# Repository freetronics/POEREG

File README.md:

Power-over-Ethernet 802.3af Regulator
=====================================

Module to regulate power supplied on Power-over-Ethernet connection
down to 10Vdc for supply to the on-board voltage regulator in an
Arduino Uno or other compatible board using the Freetronics Ethernet
Shield, or boards with onboard Ethernet such as the Freetronics
EtherTen, EtherMega, and EtherDue.

The output can optionally be switched to 12V which can be useful for
supplying power to external loads such as 12V relays.

Features:

 * Adds 802.3af-compliant Power-over-Ethernet "PD" (powered device)
   support to the Freetronics Ethernet shield and other Freetronics
   boards.
 * Input voltage range 36-57Vdc (nominal 48Vdc for 802.3af PoE)
 * Output voltage regulated to 10V and fed to Arduino on-board voltage
   regulator via Ethernet shield for further regulation down to 5V.
 * Plugs directly onto Freetronics Ethernet Shield and other
   Freetronics boards.
 * "Power on" LED.

More information at:

  http://www.freetronics.com.au/poereg

Hardware
--------
The "Hardware" directory contains the PCB design as an EAGLE project.
EAGLE PCB design software is available from Autodesk free for
non-commercial use.

Credits
-------
  * Jonathan Oxer <jon@oxer.com.au>

License
-------
Copyright 2010-2021 Freetronics Pty Ltd www.freetronics.com

The hardware portion of this project is licensed under the TAPR Open
Hardware License (www.tapr.org/OHL). The "license" folder within this
repository also contains a copy of this license in plain text format.

The software portion of this project is licensed under the Simplified
BSD License. The "licence" folder within this project contains a
copy of this license in plain text format.

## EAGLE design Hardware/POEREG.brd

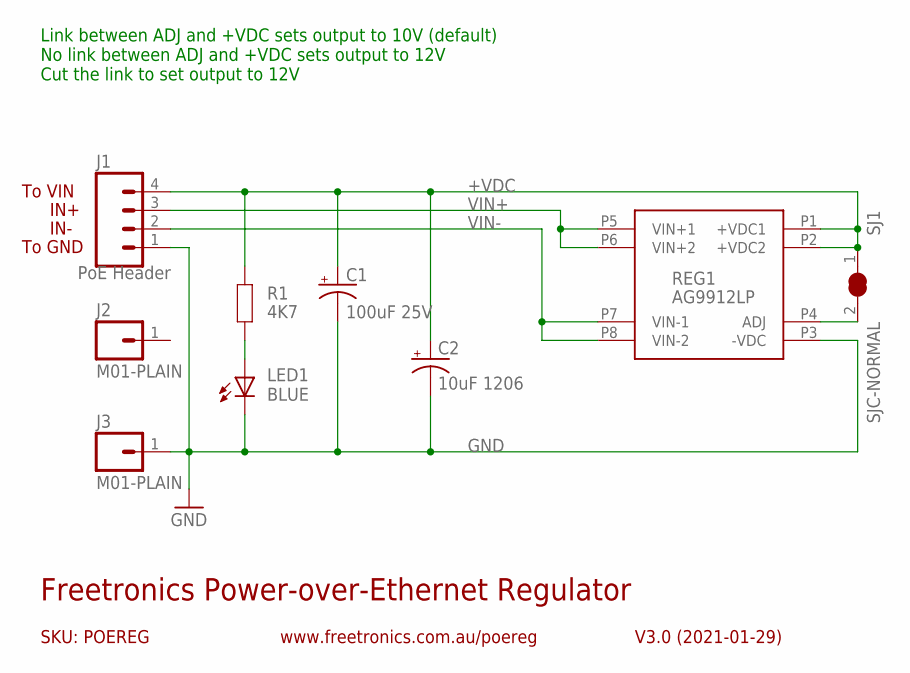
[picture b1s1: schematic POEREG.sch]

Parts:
C1: 100uF 25V; PANASONIC_D
C2: 10uF 1206; EIA3216
J1: PoE Header; 1X04
J2, J3: M01-PLAIN; 1X01
LED1: BLUE; LED-0603
R1: 4K7; R0603
REG1: AG9912LP; AG9900LP
SJ1: SJC-NORMAL; SJC

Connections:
+VDC: C1.+, C2.A (+), J1.4, R1.1, REG1.P1 (+VDC1), REG1.P2 (+VDC2), SJ1.1
GND: C1.-, C2.C (-), J1.1, J3.1, LED1.C, REG1.P3 (-VDC)
unnamed: REG1.P4 (ADJ), SJ1.2
unnamed: LED1.A, R1.2
VIN+: J1.3, REG1.P5 (VIN+1), REG1.P6 (VIN+2)
VIN-: J1.2, REG1.P7 (VIN-1), REG1.P8 (VIN-2)

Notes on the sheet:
Freetronics Power-over-Ethernet Regulator
V3.0 (2021-01-29)
www.freetronics.com.au/poereg
SKU: POEREG
To VIN
IN+
IN-
To GND
Link between ADJ and +VDC sets output to 10V (default) No link between ADJ and +VDC sets output to 12V Cut the link to set output to 12V

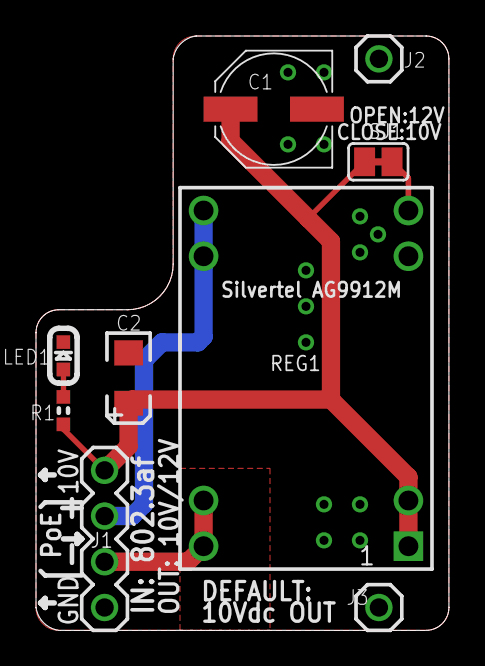
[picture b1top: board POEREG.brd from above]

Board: 2 copper layers, 22.9 x 33.0 mm, 9 parts (0 on the bottom side), 6 nets.

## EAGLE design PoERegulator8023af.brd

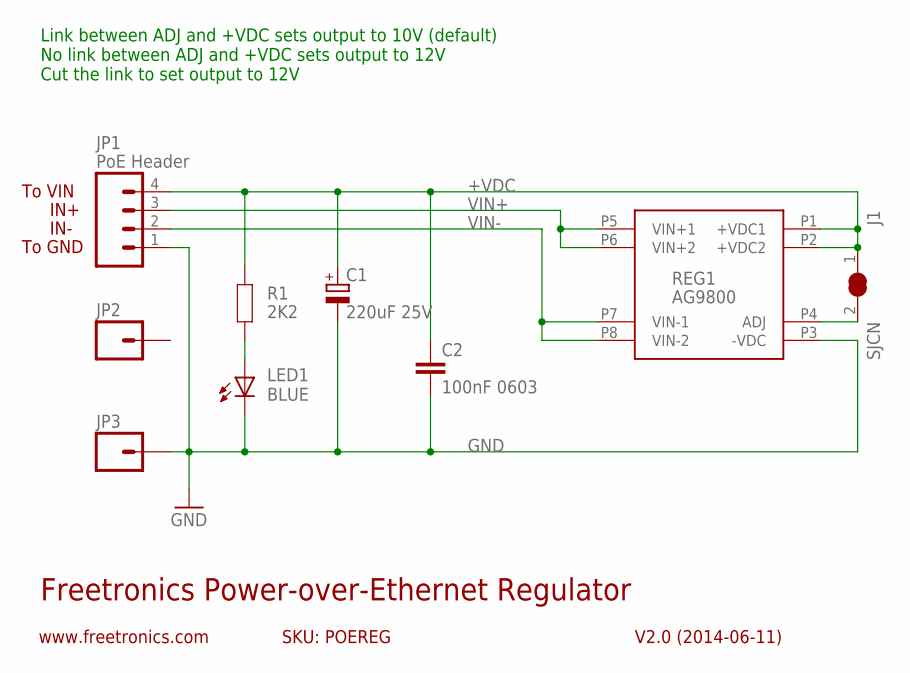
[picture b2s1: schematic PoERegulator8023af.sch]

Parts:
C1: 220uF 25V; PANASONIC_D
C2: 100nF 0603; 0603
J1: SJCN; SJC
JP1: PoE Header; 1X04
JP2, JP3: M01PTH; 1X01
LED1: BLUE; LED-0603
R1: 2K2; 0603
REG1: AG9800

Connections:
+VDC: C1.+, C2.1, J1.1, JP1.4, R1.1, REG1.P1 (+VDC1), REG1.P2 (+VDC2)
GND: C1.-, C2.2, JP1.1, JP3.1, LED1.C, REG1.P3 (-VDC)
unnamed: J1.2, REG1.P4 (ADJ)
unnamed: LED1.A, R1.2
VIN+: JP1.3, REG1.P5 (VIN+1), REG1.P6 (VIN+2)
VIN-: JP1.2, REG1.P7 (VIN-1), REG1.P8 (VIN-2)

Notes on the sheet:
Freetronics Power-over-Ethernet Regulator
V2.0 (2014-06-11)
www.freetronics.com
SKU: POEREG
To VIN
IN+
IN-
To GND
Link between ADJ and +VDC sets output to 10V (default) No link between ADJ and +VDC sets output to 12V Cut the link to set output to 12V

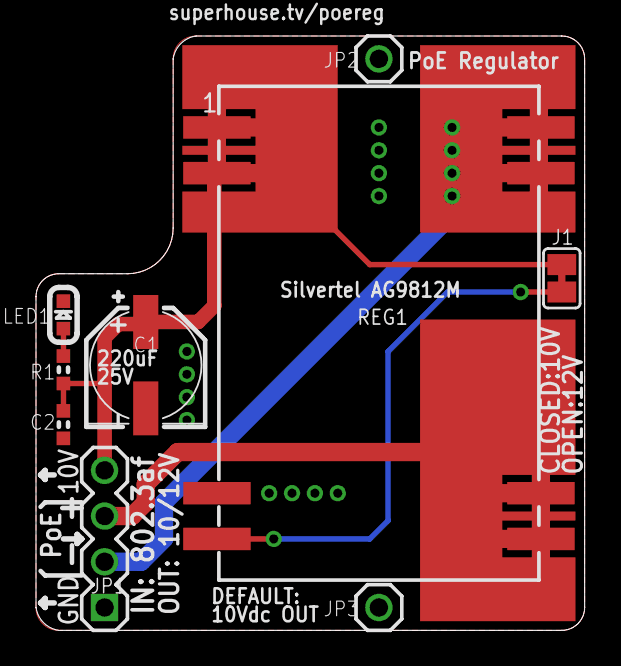
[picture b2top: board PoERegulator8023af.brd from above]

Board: 2 copper layers, 30.5 x 33.0 mm, 9 parts (0 on the bottom side), 6 nets.

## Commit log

2010-07-28 Initial import of project
2010-09-14 Updated reg part to have correct footprint
2010-09-14 Major board rearrangement, only partly done
2010-09-24 Changed output to 7.5V and finished routing
2010-09-26 Final positioning tweaks
2010-10-05 Fixed reference to output voltage
2014-06-10 Added option to change output to 12V
2014-06-10 Updated README for v2.0
2014-06-11 Replaced Silvertel AG8112M with AG9812M for v2.0 release
2016-05-26 Improved position of part value labels
2018-01-10 Updated docs for new branding
2019-04-24 Fixed fonts for silkscreen and schematic
2021-01-29 Renamed hardware files to match SKU.
2021-01-29 Replace Silvertel module with AG9912LP.
2021-01-29 Updated formatting to match current template.
2021-01-29 Updated license directory.
2021-01-29 Added .gitignore.
2021-01-29 Added images of previous versions.
2021-01-29 Added packaging example.
2021-01-29 Added guides for previous versions.
2021-01-29 Added v3.0 getting started guide.

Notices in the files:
Hardware/POEREG.brd:
(c) 2013-2021 Freetronics Pty Ltd
PoERegulator8023af.brd:
(c) 2018 SuperHouse Automation
